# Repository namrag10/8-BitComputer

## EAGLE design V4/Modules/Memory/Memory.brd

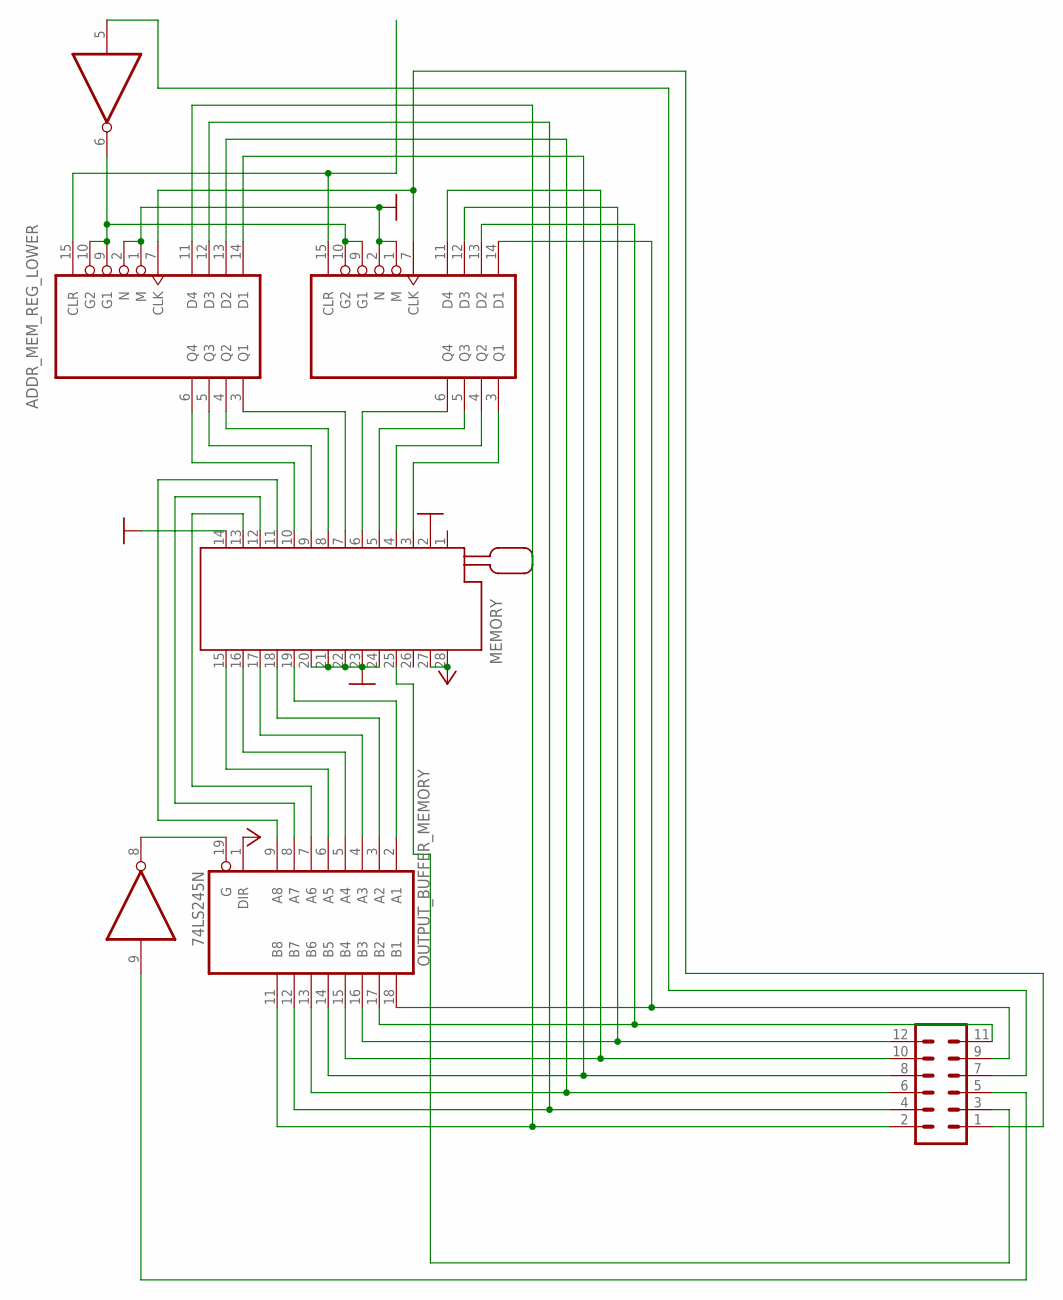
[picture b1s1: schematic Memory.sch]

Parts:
ADDR_MEM_REG_LOWER: 74LS173N; DIL16
ADDR_MEM_REG_UPPER: 74LS173N; DIL16
MEMORY: 228-1277-00-0602J
NOT_GATE1_: 74LS04N; DIL14
OUTPUT_BUFFER_MEMORY: 74LS245N; DIL20
SV1: MA06-2

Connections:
1_PLACE1: ADDR_MEM_REG_LOWER.11 (D4), OUTPUT_BUFFER_MEMORY.11 (B8), SV1.2
2_PLACE: ADDR_MEM_REG_LOWER.12 (D3), OUTPUT_BUFFER_MEMORY.12 (B7), SV1.4
4_PLACE: ADDR_MEM_REG_LOWER.13 (D2), OUTPUT_BUFFER_MEMORY.13 (B6), SV1.6
8_PLACE: ADDR_MEM_REG_LOWER.14 (D1), OUTPUT_BUFFER_MEMORY.14 (B5), SV1.8
16_PLACE: ADDR_MEM_REG_UPPER.11 (D4), OUTPUT_BUFFER_MEMORY.15 (B4), SV1.10
32_PLACE: ADDR_MEM_REG_UPPER.12 (D3), OUTPUT_BUFFER_MEMORY.16 (B3), SV1.12
64_PLACE: ADDR_MEM_REG_UPPER.13 (D2), OUTPUT_BUFFER_MEMORY.17 (B2), SV1.11
128_PLACE: ADDR_MEM_REG_UPPER.14 (D1), OUTPUT_BUFFER_MEMORY.18 (B1), SV1.9
CLOCK: ADDR_MEM_REG_LOWER.7 (CLK), ADDR_MEM_REG_UPPER.7 (CLK), SV1.1
CLR_REG: ADDR_MEM_REG_LOWER.15 (CLR), ADDR_MEM_REG_UPPER.15 (CLR)
GND: ADDR_MEM_REG_LOWER.1 (M), ADDR_MEM_REG_LOWER.2 (N), ADDR_MEM_REG_LOWER.8 (GND), ADDR_MEM_REG_UPPER.1 (M), ADDR_MEM_REG_UPPER.2 (N), ADDR_MEM_REG_UPPER.8 (GND), MEMORY.2, MEMORY.14, MEMORY.20, MEMORY.21, MEMORY.22, MEMORY.23, MEMORY.24, NOT_GATE1_.7 (GND), OUTPUT_BUFFER_MEMORY.10 (GND)
MEMORY_IN: NOT_GATE1_.5 (I), SV1.7
MEMORY_OUT: NOT_GATE1_.9 (I), SV1.5
unnamed: ADDR_MEM_REG_LOWER.6 (Q4), MEMORY.10
unnamed: ADDR_MEM_REG_LOWER.5 (Q3), MEMORY.9
unnamed: ADDR_MEM_REG_LOWER.4 (Q2), MEMORY.8
unnamed: ADDR_MEM_REG_LOWER.3 (Q1), MEMORY.7
unnamed: ADDR_MEM_REG_UPPER.6 (Q4), MEMORY.6
unnamed: ADDR_MEM_REG_UPPER.5 (Q3), MEMORY.5
unnamed: ADDR_MEM_REG_UPPER.4 (Q2), MEMORY.4
unnamed: ADDR_MEM_REG_UPPER.3 (Q1), MEMORY.3
unnamed: MEMORY.13, OUTPUT_BUFFER_MEMORY.7 (A6)
unnamed: MEMORY.12, OUTPUT_BUFFER_MEMORY.8 (A7)
unnamed: MEMORY.11, OUTPUT_BUFFER_MEMORY.9 (A8)
unnamed: MEMORY.15, OUTPUT_BUFFER_MEMORY.6 (A5)
unnamed: MEMORY.16, OUTPUT_BUFFER_MEMORY.5 (A4)
unnamed: MEMORY.17, OUTPUT_BUFFER_MEMORY.4 (A3)
unnamed: MEMORY.18, OUTPUT_BUFFER_MEMORY.3 (A2)
unnamed: MEMORY.19, OUTPUT_BUFFER_MEMORY.2 (A1)
VCC: ADDR_MEM_REG_LOWER.16 (VCC), ADDR_MEM_REG_UPPER.16 (VCC), MEMORY.27, MEMORY.28, NOT_GATE1_.14 (VCC), OUTPUT_BUFFER_MEMORY.1 (DIR), OUTPUT_BUFFER_MEMORY.20 (VCC)
~DATA/PARAM: MEMORY.25, SV1.3
~MEMORY_IN: ADDR_MEM_REG_LOWER.9 (G1), ADDR_MEM_REG_LOWER.10 (G2), ADDR_MEM_REG_UPPER.9 (G1), ADDR_MEM_REG_UPPER.10 (G2), NOT_GATE1_.6 (O)
~MEMORY_OUT: NOT_GATE1_.8 (O), OUTPUT_BUFFER_MEMORY.19 (G)

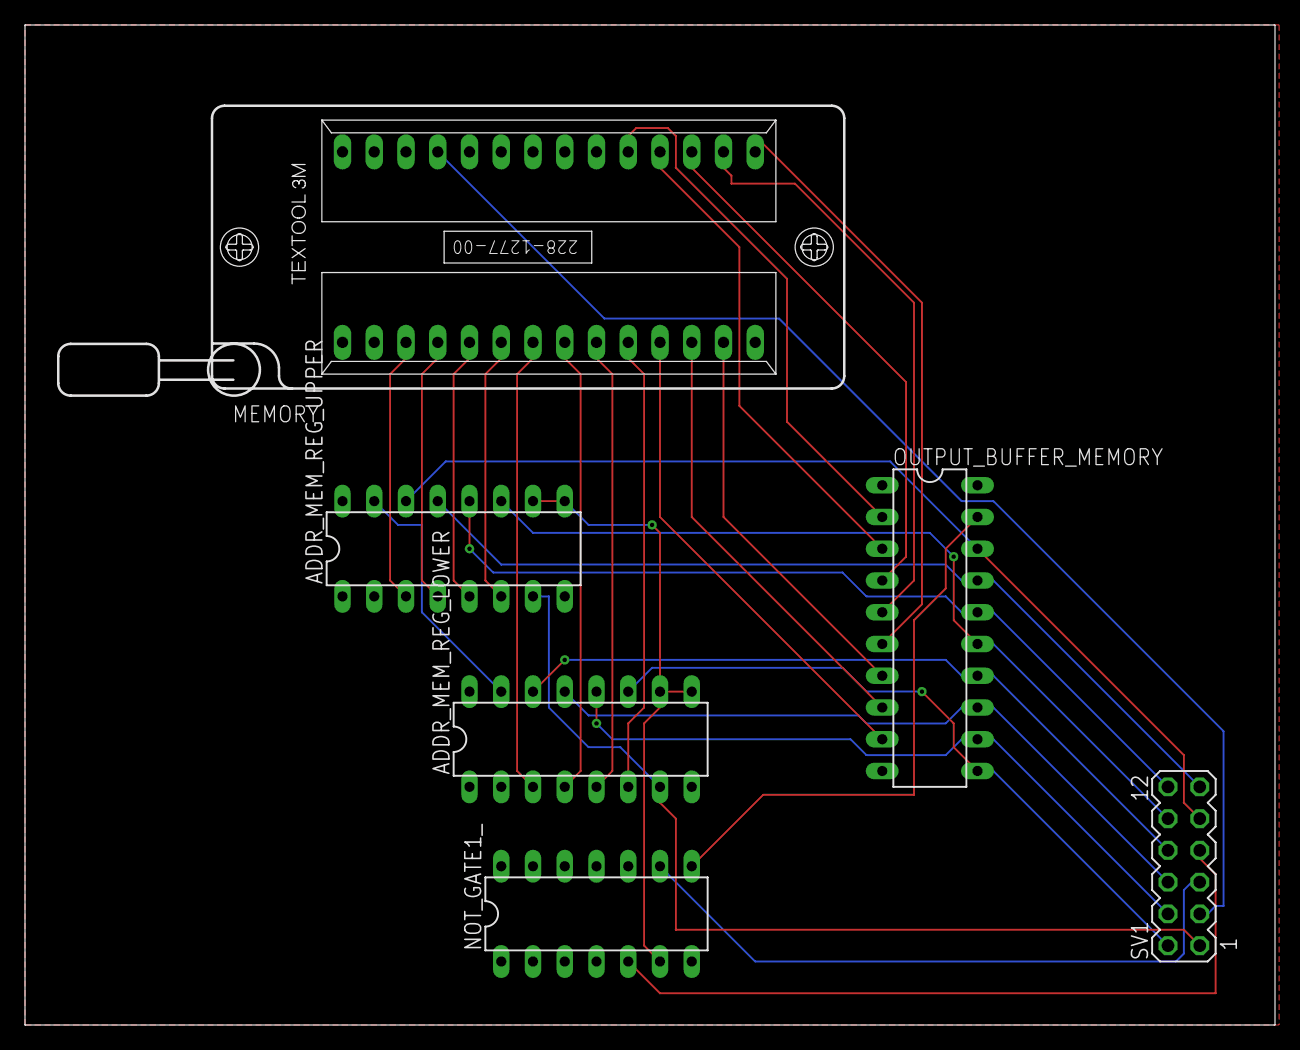
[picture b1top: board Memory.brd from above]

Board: 2 copper layers, 100.0 x 80.0 mm, 6 parts (0 on the bottom side), 33 nets.

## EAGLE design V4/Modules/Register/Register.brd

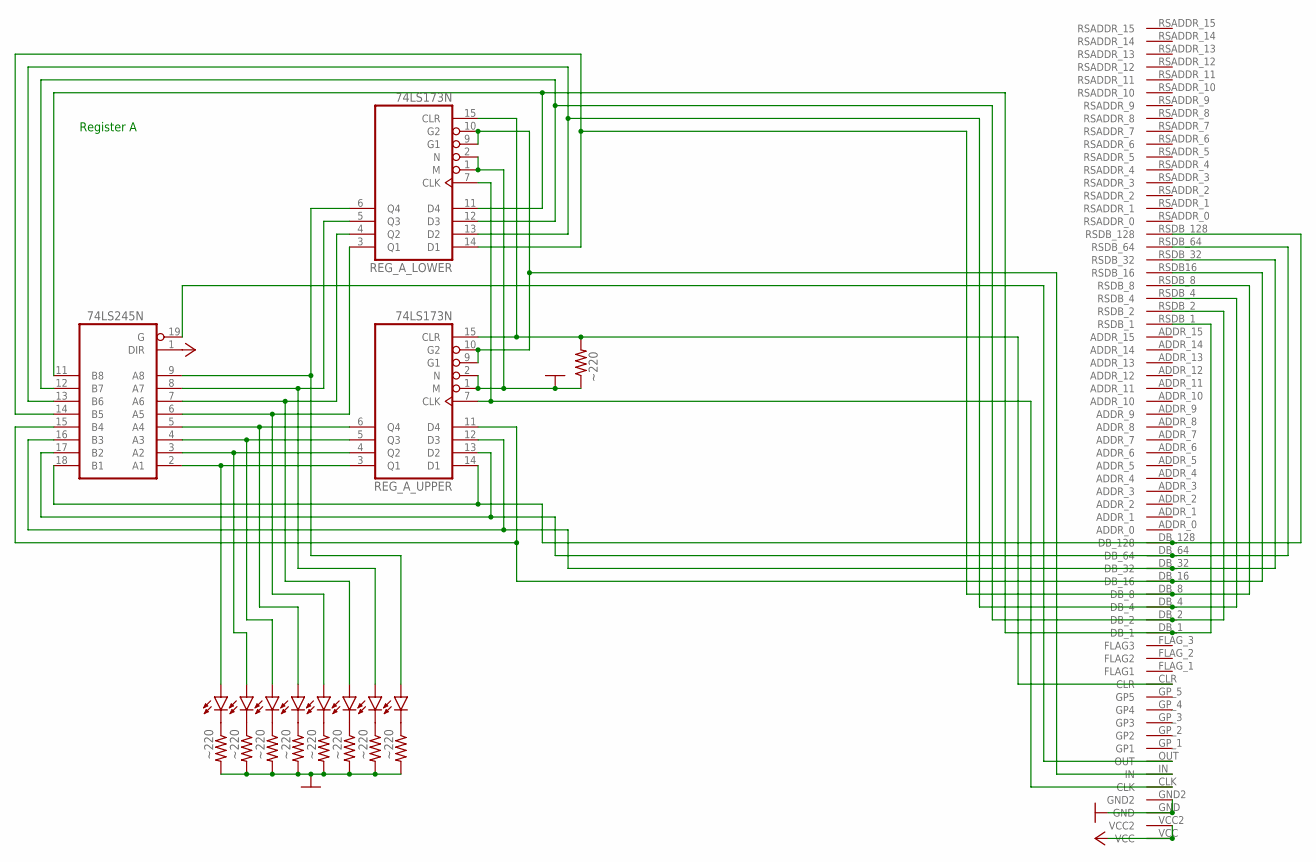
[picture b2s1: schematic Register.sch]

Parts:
LED_A_REG_1, LED_A_REG_2, LED_A_REG_3, LED_A_REG_4, LED_A_REG_5, LED_A_REG_6, LED_A_REG_7, LED_A_REG_8: LED; LED5MM
OUTPUT_BUFFER_REG_A: 74LS245N; DIL20
R1, R2, R3, R4, R5, R6, R7, R8, R9: ~220; 0204/7
REG_A_LOWER: 74LS173N; DIL16
REG_A_UPPER: 74LS173N; DIL16
U$1: BACKPLATE_INTERFACE; EDGE_FOOTPRINT

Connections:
1_PLACE1: OUTPUT_BUFFER_REG_A.11 (B8), REG_A_LOWER.11 (D4), U$1.DB_1, U$1.RSDB_1
2_PLACE: OUTPUT_BUFFER_REG_A.12 (B7), REG_A_LOWER.12 (D3), U$1.DB_2, U$1.RSDB_2
4_PLACE: OUTPUT_BUFFER_REG_A.13 (B6), REG_A_LOWER.13 (D2), U$1.DB_4, U$1.RSDB_4
8_PLACE: OUTPUT_BUFFER_REG_A.14 (B5), REG_A_LOWER.14 (D1), U$1.DB_8, U$1.RSDB_8
16_PLACE: OUTPUT_BUFFER_REG_A.15 (B4), REG_A_UPPER.11 (D4), U$1.DB_16, U$1.RSDB16 (RSDB_16)
32_PLACE: OUTPUT_BUFFER_REG_A.16 (B3), REG_A_UPPER.12 (D3), U$1.DB_32, U$1.RSDB_32
64_PLACE: OUTPUT_BUFFER_REG_A.17 (B2), REG_A_UPPER.13 (D2), U$1.DB_64, U$1.RSDB_64
128_PLACE: OUTPUT_BUFFER_REG_A.18 (B1), REG_A_UPPER.14 (D1), U$1.DB_128, U$1.RSDB_128
CLOCK: REG_A_LOWER.7 (CLK), REG_A_UPPER.7 (CLK), U$1.CLK
CLR_REG: R9.2, REG_A_LOWER.15 (CLR), REG_A_UPPER.15 (CLR), U$1.CLR
GND: OUTPUT_BUFFER_REG_A.10 (GND), R1.2, R2.2, R3.2, R4.2, R5.2, R6.2, R7.2, R8.2, R9.1, REG_A_LOWER.1 (M), REG_A_LOWER.2 (N), REG_A_LOWER.8 (GND), REG_A_UPPER.1 (M), REG_A_UPPER.2 (N), REG_A_UPPER.8 (GND), U$1.GND, U$1.GND2
unnamed: LED_A_REG_1.K (C), R1.1
unnamed: LED_A_REG_2.K (C), R2.1
unnamed: LED_A_REG_3.K (C), R3.1
unnamed: LED_A_REG_4.K (C), R4.1
unnamed: LED_A_REG_5.K (C), R5.1
unnamed: LED_A_REG_6.K (C), R6.1
unnamed: LED_A_REG_7.K (C), R7.1
unnamed: LED_A_REG_8.K (C), R8.1
REG_A_1PLACE: LED_A_REG_1.A, OUTPUT_BUFFER_REG_A.9 (A8), REG_A_LOWER.6 (Q4)
REG_A_2PLACE: LED_A_REG_2.A, OUTPUT_BUFFER_REG_A.8 (A7), REG_A_LOWER.5 (Q3)
REG_A_4PLACE: LED_A_REG_3.A, OUTPUT_BUFFER_REG_A.7 (A6), REG_A_LOWER.4 (Q2)
REG_A_8PLACE: LED_A_REG_4.A, OUTPUT_BUFFER_REG_A.6 (A5), REG_A_LOWER.3 (Q1)
REG_A_16PLACE: LED_A_REG_5.A, OUTPUT_BUFFER_REG_A.5 (A4), REG_A_UPPER.6 (Q4)
REG_A_32PLACE: LED_A_REG_6.A, OUTPUT_BUFFER_REG_A.4 (A3), REG_A_UPPER.5 (Q3)
REG_A_64PLACE: LED_A_REG_7.A, OUTPUT_BUFFER_REG_A.3 (A2), REG_A_UPPER.4 (Q2)
REG_A_128PLACE: LED_A_REG_8.A, OUTPUT_BUFFER_REG_A.2 (A1), REG_A_UPPER.3 (Q1)
REG_A_IN: REG_A_LOWER.9 (G1), REG_A_LOWER.10 (G2), REG_A_UPPER.9 (G1), REG_A_UPPER.10 (G2), U$1.IN
REG_A_OUT: OUTPUT_BUFFER_REG_A.19 (G), U$1.OUT
VCC: OUTPUT_BUFFER_REG_A.1 (DIR), OUTPUT_BUFFER_REG_A.20 (VCC), REG_A_LOWER.16 (VCC), REG_A_UPPER.16 (VCC), U$1.VCC, U$1.VCC2

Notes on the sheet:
Register A

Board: 2 copper layers, 21 parts (0 on the bottom side), 30 nets, no tracks yet.

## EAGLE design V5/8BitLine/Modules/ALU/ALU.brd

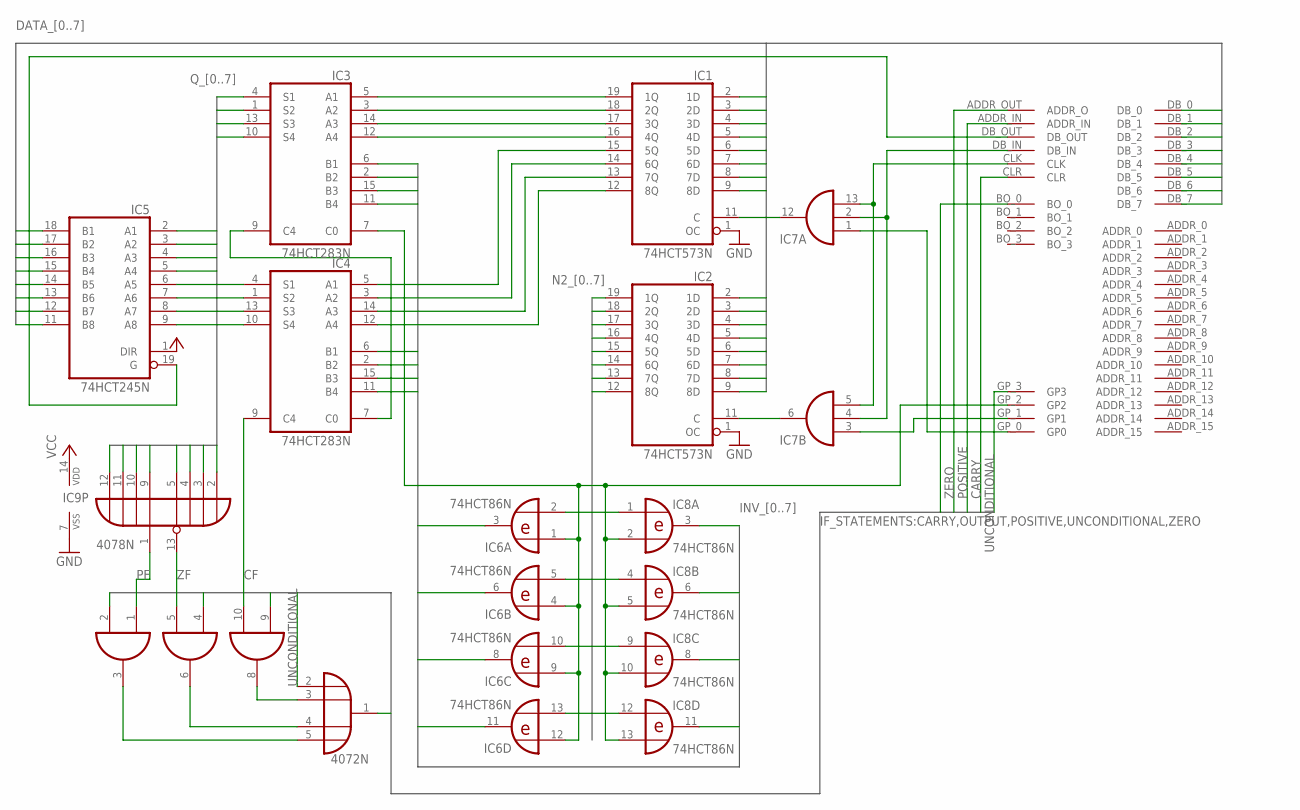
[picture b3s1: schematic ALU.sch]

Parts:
IC1, IC2: 74HCT573N; DIL20
IC3, IC4: 74HCT283N; DIL16
IC5: 74HCT245N; DIL20
IC6, IC8: 74HCT86N; DIL14
IC7: 74HCT11N; DIL14
IC9: 4078N; DIL14
IC10: 74HCT08N; DIL14
IC11: 4072N; DIL14
U$1: BACKPLATE_INTERFACEEDGE_FINGER; BACK_INTERFACE-FOOT

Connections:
CARRY: IC10.9 (I0), U$1.CLR
CF: IC4.9 (C4), IC10.10 (I1)
DATA_0: IC1.2 (1D), IC2.2 (1D), IC5.18 (B1), U$1.DB_0
DATA_1: IC1.3 (2D), IC2.3 (2D), IC5.17 (B2), U$1.DB_1
DATA_2: IC1.4 (3D), IC2.4 (3D), IC5.16 (B3), U$1.DB_2
DATA_3: IC1.5 (4D), IC2.5 (4D), IC5.15 (B4), U$1.DB_3
DATA_4: IC1.6 (5D), IC2.6 (5D), IC5.14 (B5), U$1.DB_4
DATA_5: IC1.7 (6D), IC2.7 (6D), IC5.13 (B6), U$1.DB_5
DATA_6: IC1.8 (7D), IC2.8 (7D), IC5.12 (B7), U$1.DB_6
DATA_7: IC1.9 (8D), IC2.9 (8D), IC5.11 (B8), U$1.DB_7
GND: IC1.1 (OC), IC1.10 (GND), IC2.1 (OC), IC2.10 (GND), IC3.8 (GND), IC4.8 (GND), IC5.10 (GND), IC6.7 (GND), IC7.7 (GND), IC8.7 (GND), IC9.7 (VSS), IC10.7 (GND), U$1.GND_0 (GND), U$1.GND_1 (GND)
INV_0: IC3.6 (B1), IC6.3 (O)
INV_1: IC3.2 (B2), IC6.6 (O)
INV_2: IC3.15 (B3), IC6.8 (O)
INV_3: IC3.11 (B4), IC6.11 (O)
INV_4: IC4.6 (B1), IC8.3 (O)
INV_5: IC4.2 (B2), IC8.6 (O)
INV_6: IC4.15 (B3), IC8.8 (O)
INV_7: IC4.11 (B4), IC8.11 (O)
LOWER_BYTE_SIGNAL: IC7.1 (I0), U$1.GP_0 (GP0)
N2_0: IC2.19 (1Q), IC6.2 (I1)
N2_1: IC2.18 (2Q), IC6.5 (I1)
N2_2: IC2.17 (3Q), IC6.10 (I1)
N2_3: IC2.16 (4Q), IC6.13 (I1)
N2_4: IC2.15 (5Q), IC8.1 (I0)
N2_5: IC2.14 (6Q), IC8.4 (I0)
N2_6: IC2.13 (7Q), IC8.9 (I0)
N2_7: IC2.12 (8Q), IC8.12 (I0)
unnamed: IC1.19 (1Q), IC3.5 (A1)
unnamed: IC1.18 (2Q), IC3.3 (A2)
unnamed: IC1.17 (3Q), IC3.14 (A3)
unnamed: IC1.16 (4Q), IC3.12 (A4)
unnamed: IC1.15 (5Q), IC4.5 (A1)
unnamed: IC1.14 (6Q), IC4.3 (A2)
unnamed: IC1.13 (7Q), IC4.14 (A3)
unnamed: IC1.12 (8Q), IC4.12 (A4)
unnamed: IC7.5 (I2), IC7.13 (I2), U$1.CLK
unnamed: IC7.2 (I1), IC7.4 (I1), U$1.DB_IN
unnamed: IC10.8 (O), IC11.3 (I1)
unnamed: IC10.6 (O), IC11.4 (I2)
unnamed: IC1.11 (C), IC7.12 (O)
unnamed: IC2.11 (C), IC7.6 (O)
unnamed: IC5.19 (G), U$1.DB_OUT
unnamed: IC10.3 (O), IC11.5 (I3)
unnamed: IC3.9 (C4), IC4.7 (C0)
OUTPUT: IC11.1 (O), U$1.BO_0
PF: IC9.1, IC10.1 (I0)
POSITIVE: IC10.2 (I1), U$1.ADDR_IN
Q_0: IC3.4 (S1), IC5.2 (A1), IC9.2 (I0)
Q_1: IC3.1 (S2), IC5.3 (A2), IC9.3 (I1)
Q_2: IC3.13 (S3), IC5.4 (A3), IC9.4 (I2)
Q_3: IC3.10 (S4), IC5.5 (A4), IC9.5 (I3)
Q_4: IC4.4 (S1), IC5.6 (A5), IC9.9 (I4)
Q_5: IC4.1 (S2), IC5.7 (A6), IC9.10 (I5)
Q_6: IC4.13 (S3), IC5.8 (A7), IC9.11 (I6)
Q_7: IC4.10 (S4), IC5.9 (A8), IC9.12 (I7)
SUBTRACT_MODE: IC3.7 (C0), IC6.1 (I0), IC6.4 (I0), IC6.9 (I0), IC6.12 (I0), IC8.2 (I1), IC8.5 (I1), IC8.10 (I1), IC8.13 (I1), U$1.GP_2 (GP2)
UNCONDITIONAL: IC11.2 (I0), U$1.GP_3 (GP3)
UPPER_BYTE_SIGNAL: IC7.3 (I0), U$1.GP_1 (GP1)
VCC: IC1.20 (VCC), IC2.20 (VCC), IC3.16 (VCC), IC4.16 (VCC), IC5.1 (DIR), IC5.20 (VCC), IC6.14 (VCC), IC7.14 (VCC), IC8.14 (VCC), IC9.14 (VDD), IC10.14 (VCC), U$1.VCC_0 (VCC), U$1.VCC_1 (VCC)
VDD: IC11.14 (VDD)
VSS: IC11.7 (VSS)
ZERO: IC10.4 (I0), U$1.ADDR_OUT (ADDR_O)
ZF: IC9.13 (J), IC10.5 (I1)

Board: 2 copper layers, 12 parts (0 on the bottom side), 62 nets, no tracks yet.

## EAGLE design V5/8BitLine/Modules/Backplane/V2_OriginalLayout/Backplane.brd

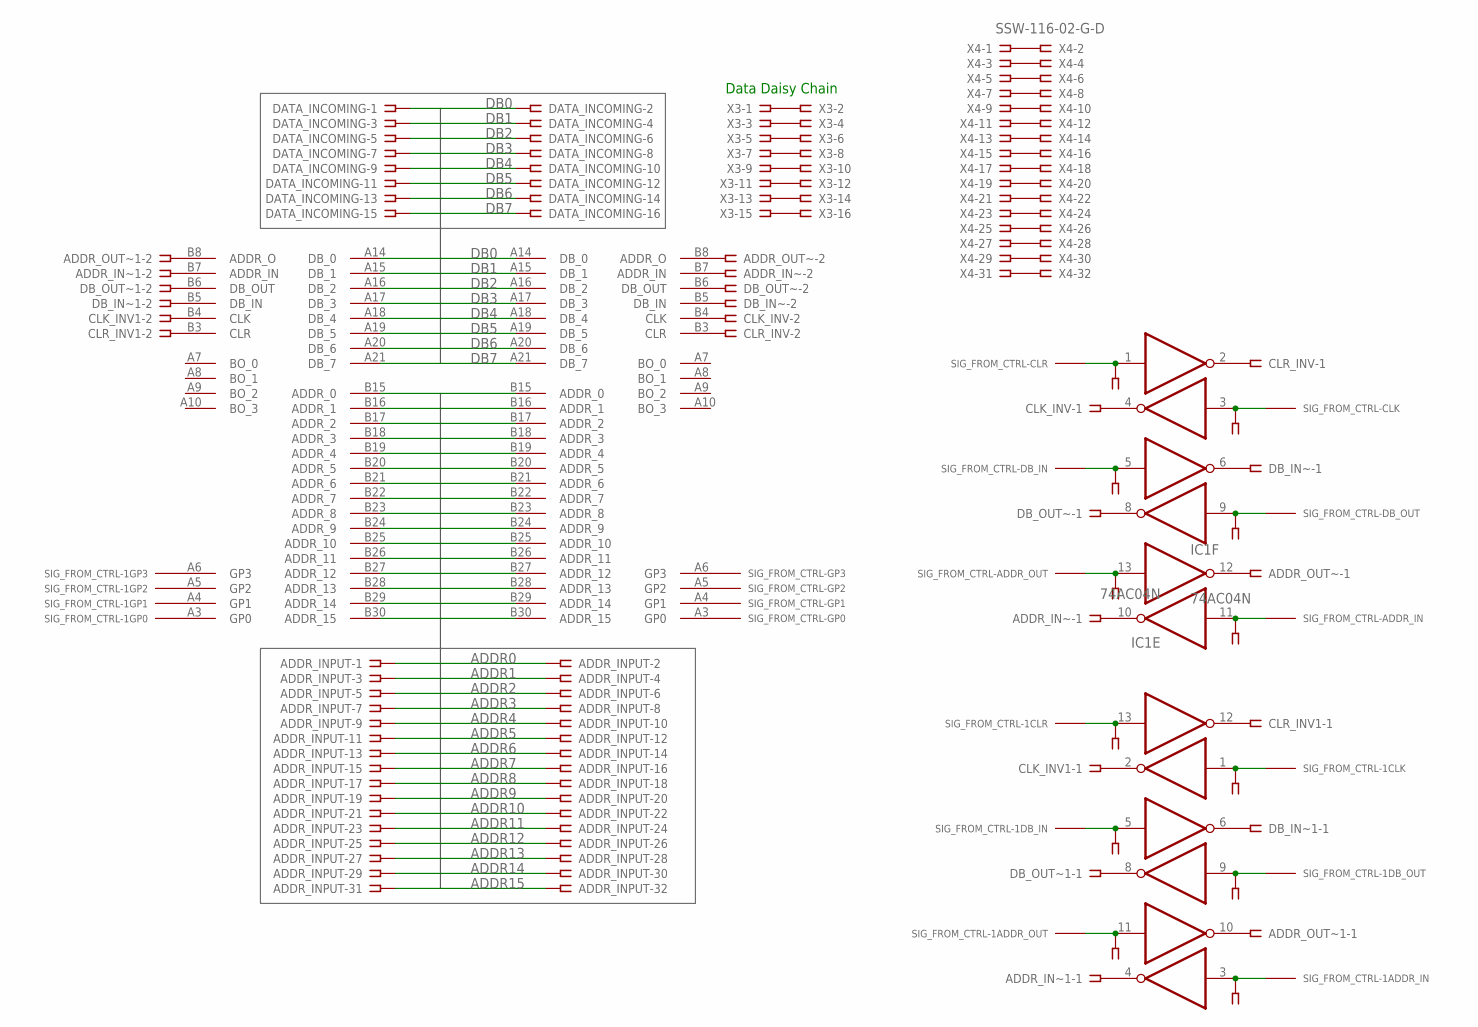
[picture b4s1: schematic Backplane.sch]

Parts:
ADDR_INPUT: SSW-116-02-G-D
ADDR_IN~, ADDR_IN~1: SSW-103-02-G-S
ADDR_OUT~, ADDR_OUT~1: SSW-103-02-G-S
CLK_INV, CLK_INV1: SSW-103-02-G-S
CLR_INV, CLR_INV1: SSW-103-02-G-S
DATA_INCOMING: SSW-108-02-G-D
DB_IN~, DB_IN~1: SSW-103-02-G-S
DB_OUT~, DB_OUT~1: SSW-103-02-G-S
IC1, IC2: 74AC04N; DIL14
SIG_FROM_CTRL-, SIG_FROM_CTRL-1: CONTROL_SIG-INT; CONTROL_SIG-INT-FOOT
U$1, U$2: BACKPLATE_INTERFACEHEADER; PCI_INTERFACE
X3: SSW-108-02-G-D
X4: SSW-116-02-G-D

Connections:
ADDR0: ADDR_INPUT.1, ADDR_INPUT.2, U$1.B15 (ADDR_0), U$2.B15 (ADDR_0)
ADDR1: ADDR_INPUT.3, ADDR_INPUT.4, U$1.B16 (ADDR_1), U$2.B16 (ADDR_1)
ADDR2: ADDR_INPUT.5, ADDR_INPUT.6, U$1.B17 (ADDR_2), U$2.B17 (ADDR_2)
ADDR3: ADDR_INPUT.7, ADDR_INPUT.8, U$1.B18 (ADDR_3), U$2.B18 (ADDR_3)
ADDR4: ADDR_INPUT.9, ADDR_INPUT.10, U$1.B19 (ADDR_4), U$2.B19 (ADDR_4)
ADDR5: ADDR_INPUT.11, ADDR_INPUT.12, U$1.B20 (ADDR_5), U$2.B20 (ADDR_5)
ADDR6: ADDR_INPUT.13, ADDR_INPUT.14, U$1.B21 (ADDR_6), U$2.B21 (ADDR_6)
ADDR7: ADDR_INPUT.15, ADDR_INPUT.16, U$1.B22 (ADDR_7), U$2.B22 (ADDR_7)
ADDR8: ADDR_INPUT.17, ADDR_INPUT.18, U$1.B23 (ADDR_8), U$2.B23 (ADDR_8)
ADDR9: ADDR_INPUT.19, ADDR_INPUT.20, U$1.B24 (ADDR_9), U$2.B24 (ADDR_9)
ADDR10: ADDR_INPUT.21, ADDR_INPUT.22, U$1.B25 (ADDR_10), U$2.B25 (ADDR_10)
ADDR11: ADDR_INPUT.23, ADDR_INPUT.24, U$1.B26 (ADDR_11), U$2.B26 (ADDR_11)
ADDR12: ADDR_INPUT.25, ADDR_INPUT.26, U$1.B27 (ADDR_12), U$2.B27 (ADDR_12)
ADDR13: ADDR_INPUT.27, ADDR_INPUT.28, U$1.B28 (ADDR_13), U$2.B28 (ADDR_13)
ADDR14: ADDR_INPUT.29, ADDR_INPUT.30, U$1.B29 (ADDR_14), U$2.B29 (ADDR_14)
ADDR15: ADDR_INPUT.31, ADDR_INPUT.32, U$1.B30 (ADDR_15), U$2.B30 (ADDR_15)
DB0: DATA_INCOMING.1, DATA_INCOMING.2, U$1.A14 (DB_0), U$2.A14 (DB_0)
DB1: DATA_INCOMING.3, DATA_INCOMING.4, U$1.A15 (DB_1), U$2.A15 (DB_1)
DB2: DATA_INCOMING.5, DATA_INCOMING.6, U$1.A16 (DB_2), U$2.A16 (DB_2)
DB3: DATA_INCOMING.7, DATA_INCOMING.8, U$1.A17 (DB_3), U$2.A17 (DB_3)
DB4: DATA_INCOMING.9, DATA_INCOMING.10, U$1.A18 (DB_4), U$2.A18 (DB_4)
DB5: DATA_INCOMING.11, DATA_INCOMING.12, U$1.A19 (DB_5), U$2.A19 (DB_5)
DB6: DATA_INCOMING.13, DATA_INCOMING.14, U$1.A20 (DB_6), U$2.A20 (DB_6)
DB7: DATA_INCOMING.15, DATA_INCOMING.16, U$1.A21 (DB_7), U$2.A21 (DB_7)
GND: IC1.7 (GND), IC2.7 (GND), SIG_FROM_CTRL-.GND, SIG_FROM_CTRL-1.GND, U$1.B2 (GND), U$1.B31 (GND), U$2.B2 (GND), U$2.B31 (GND)
unnamed: CLR_INV.2, U$2.B3 (CLR)
unnamed: CLR_INV.3, IC1.1 (I), SIG_FROM_CTRL-.CLR (0)
unnamed: CLK_INV.2, U$2.B4 (CLK)
unnamed: DB_IN~.2, U$2.B5 (DB_IN)
unnamed: DB_OUT~.2, U$2.B6 (DB_OUT)
unnamed: SIG_FROM_CTRL-.GP0 (0), U$2.A3 (GP0)
unnamed: SIG_FROM_CTRL-.GP1 (0), U$2.A4 (GP1)
unnamed: CLK_INV.3, IC1.3 (I), SIG_FROM_CTRL-.CLK (0)
unnamed: DB_IN~.3, IC1.5 (I), SIG_FROM_CTRL-.DB_IN (0)
unnamed: DB_OUT~.3, IC1.9 (I), SIG_FROM_CTRL-.DB_OUT (0)
unnamed: SIG_FROM_CTRL-.GP2 (0), U$2.A5 (GP2)
unnamed: SIG_FROM_CTRL-.GP3 (0), U$2.A6 (GP3)
unnamed: ADDR_OUT~.3, IC1.13 (I), SIG_FROM_CTRL-.ADDR_OT (0)
unnamed: ADDR_IN~.1, IC1.10 (O)
unnamed: CLR_INV.1, IC1.2 (O)
unnamed: CLK_INV.1, IC1.4 (O)
unnamed: DB_IN~.1, IC1.6 (O)
unnamed: DB_OUT~.1, IC1.8 (O)
unnamed: ADDR_IN~.3, IC1.11 (I), SIG_FROM_CTRL-.ADDR_IN (0)
unnamed: ADDR_OUT~.1, IC1.12 (O)
unnamed: ADDR_OUT~.2, U$2.B8 (ADDR_O)
unnamed: ADDR_IN~.2, U$2.B7 (ADDR_IN)
unnamed: X3.1, X3.2
unnamed: X3.3, X3.4
unnamed: X3.5, X3.6
unnamed: X3.7, X3.8
unnamed: X3.9, X3.10
unnamed: X3.11, X3.12
unnamed: X3.13, X3.14
unnamed: X3.15, X3.16
unnamed: X4.1, X4.2
unnamed: X4.3, X4.4
unnamed: X4.5, X4.6
unnamed: X4.7, X4.8
unnamed: X4.9, X4.10
unnamed: X4.11, X4.12
unnamed: X4.13, X4.14
unnamed: X4.15, X4.16
unnamed: X4.17, X4.18
unnamed: X4.19, X4.20
unnamed: X4.21, X4.22
unnamed: X4.23, X4.24
unnamed: X4.25, X4.26
unnamed: X4.27, X4.28
unnamed: X4.29, X4.30
unnamed: X4.31, X4.32
unnamed: CLR_INV1.3, IC2.13 (I), SIG_FROM_CTRL-1.CLR (0)
unnamed: CLK_INV1.3, IC2.1 (I), SIG_FROM_CTRL-1.CLK (0)
unnamed: DB_IN~1.3, IC2.5 (I), SIG_FROM_CTRL-1.DB_IN (0)
unnamed: DB_OUT~1.3, IC2.9 (I), SIG_FROM_CTRL-1.DB_OUT (0)
unnamed: CLK_INV1.1, IC2.2 (O)
unnamed: ADDR_IN~1.1, IC2.4 (O)
unnamed: DB_IN~1.1, IC2.6 (O)
unnamed: DB_OUT~1.1, IC2.8 (O)
unnamed: ADDR_OUT~1.3, IC2.11 (I), SIG_FROM_CTRL-1.ADDR_OT (0)
unnamed: ADDR_IN~1.3, IC2.3 (I), SIG_FROM_CTRL-1.ADDR_IN (0)
unnamed: ADDR_OUT~1.1, IC2.10 (O)
unnamed: CLR_INV1.1, IC2.12 (O)
unnamed: CLK_INV1.2, U$1.B4 (CLK)
unnamed: CLR_INV1.2, U$1.B3 (CLR)
unnamed: DB_IN~1.2, U$1.B5 (DB_IN)
unnamed: DB_OUT~1.2, U$1.B6 (DB_OUT)
unnamed: ADDR_OUT~1.2, U$1.B8 (ADDR_O)
unnamed: ADDR_IN~1.2, U$1.B7 (ADDR_IN)
unnamed: SIG_FROM_CTRL-1.GP0 (0), U$1.A3 (GP0)
unnamed: SIG_FROM_CTRL-1.GP1 (0), U$1.A4 (GP1)
unnamed: SIG_FROM_CTRL-1.GP2 (0), U$1.A5 (GP2)
unnamed: SIG_FROM_CTRL-1.GP3 (0), U$1.A6 (GP3)
VCC: IC1.14 (VCC), IC2.14 (VCC), SIG_FROM_CTRL-.VCC, SIG_FROM_CTRL-1.VCC, U$1.A2 (VCC), U$1.A31 (VCC), U$2.A2 (VCC), U$2.A31 (VCC)

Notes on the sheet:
Data Daisy Chain

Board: 2 copper layers, 22 parts (0 on the bottom side), 94 nets, no tracks yet.

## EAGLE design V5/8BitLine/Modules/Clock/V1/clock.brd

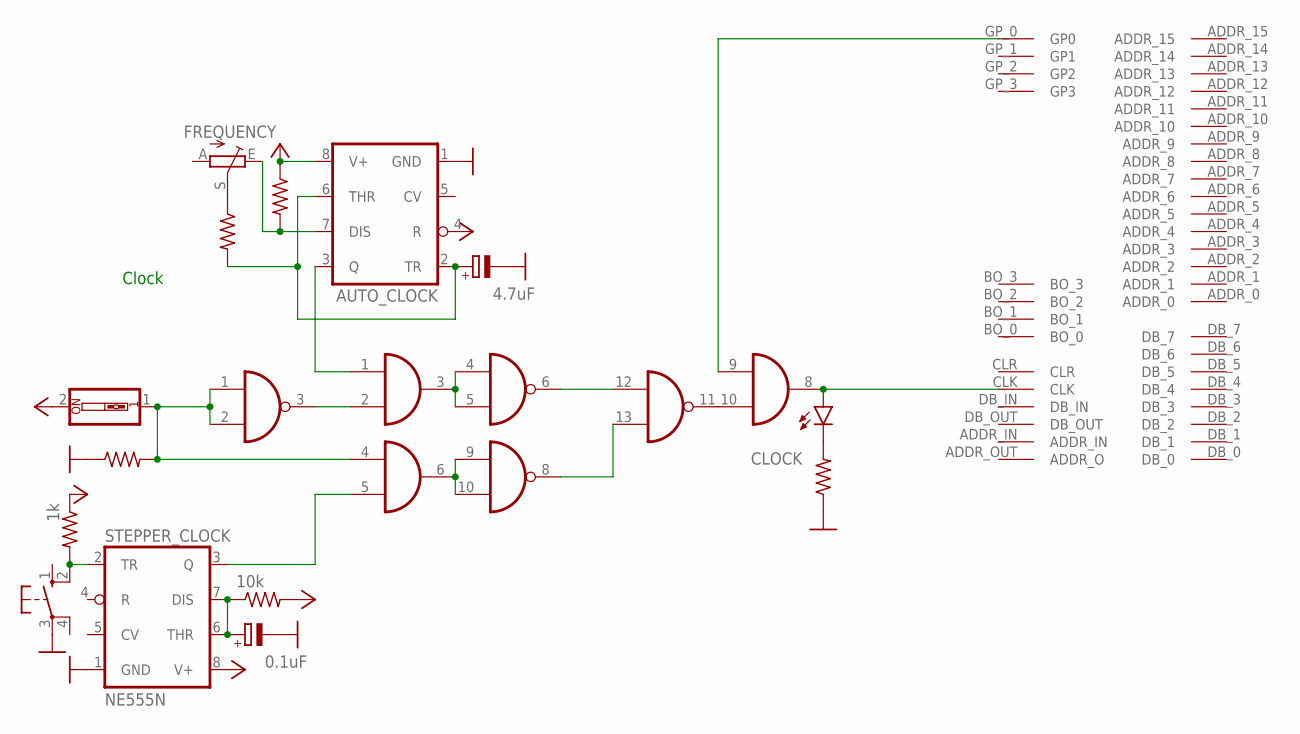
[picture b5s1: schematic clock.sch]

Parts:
AND_GATE_: 74LS08N; DIL14
AUTO_CLOCK: NE555N; DIL08
C1: 4.7uF; E2-5
C2: 0.1uF; E2-5
CLK_MODE: SWITCH; EDG-01
CLK_TRIGGER: SWITCH; B3F-10XX
CLOCK: Yellow; LED5MM
FREQUENCY: 100k; RJ9W
NAND: 74ACT00N; DIL14
R1, R2: 1k; 0204/7
R3: 10k; 0204/7
R4, R6: 220; 0204/7
R5: ~220; 0204/7
STEPPER_CLOCK: NE555N; DIL08
U$1: BACKPLATE_INTERFACEEDGE_FINGER; BACK_INTERFACE-FOOT

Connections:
CLOCK: AND_GATE_.8 (O), CLOCK.A, U$1.CLK
GND: AND_GATE_.7 (GND), AUTO_CLOCK.1 (GND), C1.-, C2.-, CLK_TRIGGER.3, NAND.7 (GND), R4.1, R5.1, STEPPER_CLOCK.1 (GND), U$1.GND_0 (GND), U$1.GND_1 (GND)
HLT: AND_GATE_.9 (I0), U$1.GP_0 (GP0)
MODE_SIGNAL: AND_GATE_.4 (I0), CLK_MODE.1, NAND.1 (I0), NAND.2 (I1), R4.2
unnamed: C2.+, R3.1, STEPPER_CLOCK.6 (THR), STEPPER_CLOCK.7 (DIS)
unnamed: CLK_TRIGGER.2 (S1), R2.2, STEPPER_CLOCK.2 (TR)
unnamed: CLOCK.K (C), R5.2
unnamed: AND_GATE_.5 (I1), STEPPER_CLOCK.3 (Q)
unnamed: AND_GATE_.3 (O), NAND.4 (I0), NAND.5 (I1)
unnamed: AND_GATE_.1 (I0), AUTO_CLOCK.3 (Q)
unnamed: AND_GATE_.6 (O), NAND.9 (I0), NAND.10 (I1)
unnamed: NAND.8 (O), NAND.13 (I1)
unnamed: AND_GATE_.2 (I1), NAND.3 (O)
unnamed: NAND.6 (O), NAND.12 (I0)
unnamed: AND_GATE_.10 (I1), NAND.11 (O)
unnamed: AUTO_CLOCK.2 (TR), AUTO_CLOCK.6 (THR), C1.+, R6.2
unnamed: FREQUENCY.S, R6.1
unnamed: AUTO_CLOCK.7 (DIS), FREQUENCY.E, R1.2
VCC: AND_GATE_.14 (VCC), AUTO_CLOCK.4 (R), AUTO_CLOCK.8 (V+), CLK_MODE.2, NAND.14 (VCC), R1.1, R2.1, R3.2, STEPPER_CLOCK.8 (V+), U$1.VCC_0 (VCC), U$1.VCC_1 (VCC)

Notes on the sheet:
Clock

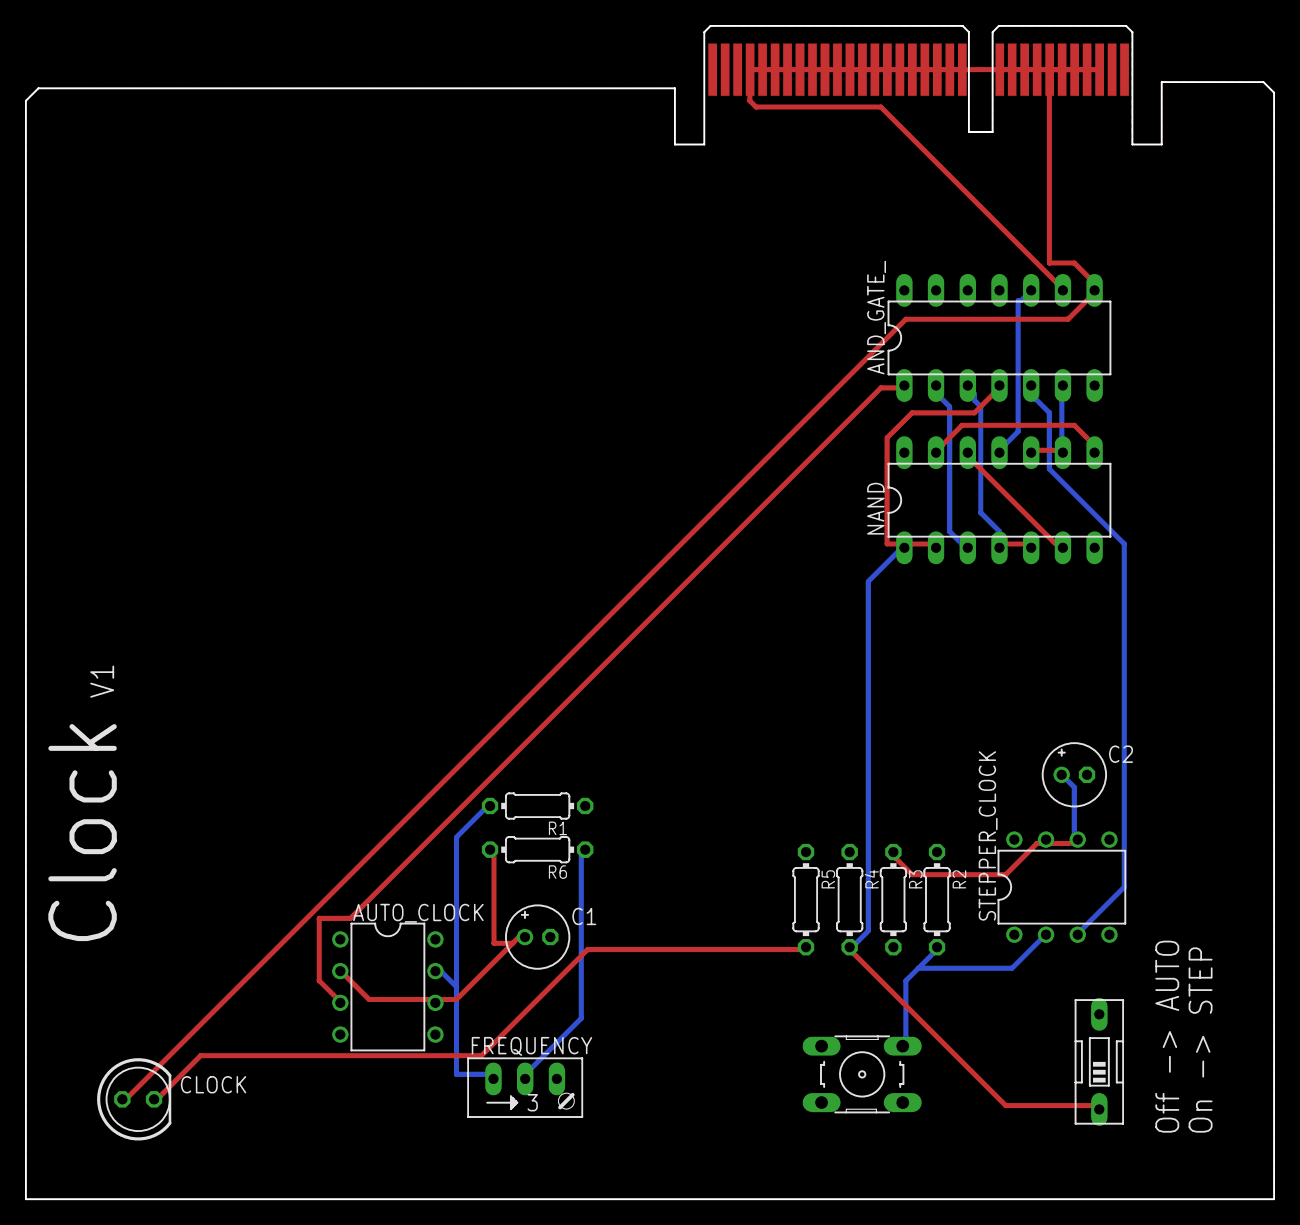
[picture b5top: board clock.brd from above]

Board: 2 copper layers, 100.0 x 94.0 mm, 17 parts (0 on the bottom side), 19 nets.

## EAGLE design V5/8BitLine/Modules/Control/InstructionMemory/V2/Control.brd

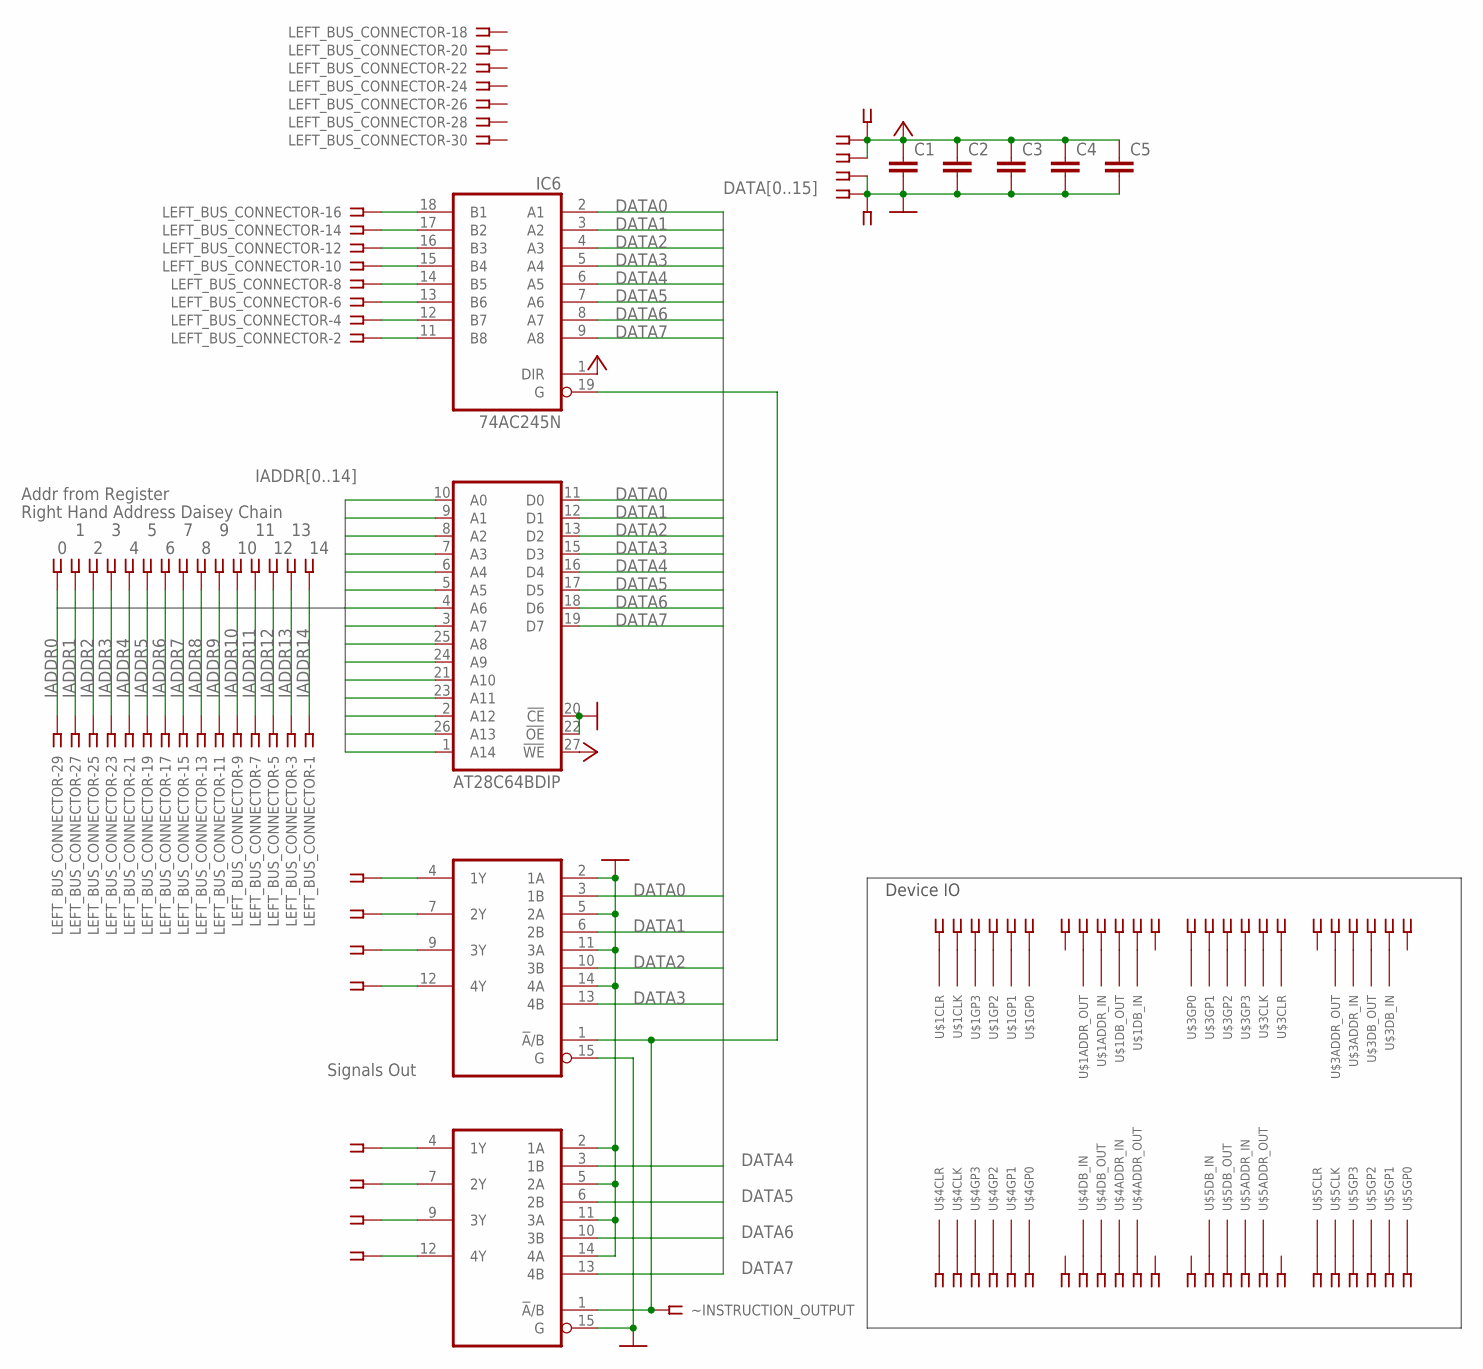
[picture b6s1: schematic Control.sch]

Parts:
C1, C2, C3, C4, C5: C2.5/2; C2.5-2
IC4, IC5: 74AC157N; DIL16
IC6: 74AC245N; DIL20
LEFT_BUS_CONNECTOR: SSW-115-02-G-D
MEZZANINE: SSW-104-02-G-S
U$1, U$3, U$4, U$5: CONTROL_SIG-INT; CONTROL_SIG-INT-FOOT
U$2: AT28C64BDIP; DIP28-WIDE
X1, X2, X3, X4, X6, X7, X8, X9: SSW-106-02-G-S
X5: SSW-108-02-G-S
X11: SSW-102-02-G-S
X12: SSW-115-02-G-S
~INSTRUCTION_OUTPUT: SSW-101-02-G-S

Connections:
DATA0: IC4.3 (1B), IC6.2 (A1), U$2.11 (D0)
DATA1: IC4.6 (2B), IC6.3 (A2), U$2.12 (D1)
DATA2: IC4.10 (3B), IC6.4 (A3), U$2.13 (D2)
DATA3: IC4.13 (4B), IC6.5 (A4), U$2.15 (D3)
DATA4: IC5.3 (1B), IC6.6 (A5), U$2.16 (D4)
DATA5: IC5.6 (2B), IC6.7 (A6), U$2.17 (D5)
DATA6: IC5.10 (3B), IC6.8 (A7), U$2.18 (D6)
DATA7: IC5.13 (4B), IC6.9 (A8), U$2.19 (D7)
GND: C1.2, C2.2, C3.2, C4.2, C5.2, IC4.2 (1A), IC4.5 (2A), IC4.8 (GND), IC4.11 (3A), IC4.14 (4A), IC4.15 (G), IC5.2 (1A), IC5.5 (2A), IC5.8 (GND), IC5.11 (3A), IC5.14 (4A), IC5.15 (G), IC6.10 (GND), MEZZANINE.3, MEZZANINE.4, U$1.GND, U$2.14 (GND), U$2.20 (!CE), U$2.22 (!OE), U$3.GND, U$4.GND, U$5.GND, X11.2
IADDR0: LEFT_BUS_CONNECTOR.29, U$2.10 (A0), X12.1
IADDR1: LEFT_BUS_CONNECTOR.27, U$2.9 (A1), X12.2
IADDR2: LEFT_BUS_CONNECTOR.25, U$2.8 (A2), X12.3
IADDR3: LEFT_BUS_CONNECTOR.23, U$2.7 (A3), X12.4
IADDR4: LEFT_BUS_CONNECTOR.21, U$2.6 (A4), X12.5
IADDR5: LEFT_BUS_CONNECTOR.19, U$2.5 (A5), X12.6
IADDR6: LEFT_BUS_CONNECTOR.17, U$2.4 (A6), X12.7
IADDR7: LEFT_BUS_CONNECTOR.15, U$2.3 (A7), X12.8
IADDR8: LEFT_BUS_CONNECTOR.13, U$2.25 (A8), X12.9
IADDR9: LEFT_BUS_CONNECTOR.11, U$2.24 (A9), X12.10
IADDR10: LEFT_BUS_CONNECTOR.9, U$2.21 (A10), X12.11
IADDR11: LEFT_BUS_CONNECTOR.7, U$2.23 (A11), X12.12
IADDR12: LEFT_BUS_CONNECTOR.5, U$2.2 (A12), X12.13
IADDR13: LEFT_BUS_CONNECTOR.3, U$2.26 (A13), X12.14
IADDR14: LEFT_BUS_CONNECTOR.1, U$2.1 (A14), X12.15
I_OUT: IC4.1 (!A!/B), IC5.1 (!A!/B), IC6.19 (G), ~INSTRUCTION_OUTPUT.1
unnamed: U$1.GP0 (0), X1.6
unnamed: U$1.GP1 (0), X1.5
unnamed: U$1.GP2 (0), X1.4
unnamed: U$1.GP3 (0), X1.3
unnamed: U$1.CLK (0), X1.2
unnamed: U$1.CLR (0), X1.1
unnamed: U$1.DB_IN (0), X2.2
unnamed: U$1.DB_OUT (0), X2.3
unnamed: U$1.ADDR_IN (0), X2.4
unnamed: U$1.ADDR_OT (0), X2.5
unnamed: U$3.GP0 (0), X3.6
unnamed: U$3.GP1 (0), X3.5
unnamed: U$3.GP2 (0), X3.4
unnamed: U$3.GP3 (0), X3.3
unnamed: U$3.CLK (0), X3.2
unnamed: U$3.CLR (0), X3.1
unnamed: U$3.DB_IN (0), X4.2
unnamed: U$3.DB_OUT (0), X4.3
unnamed: U$3.ADDR_IN (0), X4.4
unnamed: U$3.ADDR_OT (0), X4.5
unnamed: U$4.CLR (0), X9.1
unnamed: U$4.CLK (0), X9.2
unnamed: U$4.GP0 (0), X9.6
unnamed: U$4.GP1 (0), X9.5
unnamed: U$4.GP2 (0), X9.4
unnamed: U$4.GP3 (0), X9.3
unnamed: U$4.DB_IN (0), X8.2
unnamed: U$4.DB_OUT (0), X8.3
unnamed: U$4.ADDR_IN (0), X8.4
unnamed: U$4.ADDR_OT (0), X8.5
unnamed: U$5.GP0 (0), X6.6
unnamed: U$5.GP3 (0), X6.3
unnamed: U$5.GP2 (0), X6.4
unnamed: U$5.GP1 (0), X6.5
unnamed: U$5.CLK (0), X6.2
unnamed: U$5.CLR (0), X6.1
unnamed: U$5.DB_IN (0), X7.2
unnamed: U$5.DB_OUT (0), X7.3
unnamed: U$5.ADDR_IN (0), X7.4
unnamed: U$5.ADDR_OT (0), X7.5
O_DB0: IC6.18 (B1), LEFT_BUS_CONNECTOR.16
O_DB1: IC6.17 (B2), LEFT_BUS_CONNECTOR.14
O_DB2: IC6.16 (B3), LEFT_BUS_CONNECTOR.12
O_DB3: IC6.15 (B4), LEFT_BUS_CONNECTOR.10
O_DB4: IC6.14 (B5), LEFT_BUS_CONNECTOR.8
O_DB5: IC6.13 (B6), LEFT_BUS_CONNECTOR.6
O_DB6: IC6.12 (B7), LEFT_BUS_CONNECTOR.4
O_DB7: IC6.11 (B8), LEFT_BUS_CONNECTOR.2
SIG_1: IC4.4 (1Y), X5.1
SIG_2: IC4.7 (2Y), X5.2
SIG_3: IC4.9 (3Y), X5.3
SIG_4: IC4.12 (4Y), X5.4
SIG_5: IC5.4 (1Y), X5.5
SIG_6: IC5.7 (2Y), X5.6
SIG_7: IC5.9 (3Y), X5.7
SIG_8: IC5.12 (4Y), X5.8
VCC: C1.1, C2.1, C3.1, C4.1, C5.1, IC4.16 (VCC), IC5.16 (VCC), IC6.1 (DIR), IC6.20 (VCC), MEZZANINE.1, MEZZANINE.2, U$1.VCC, U$2.27 (!WE), U$2.28 (VCC), U$3.VCC, U$4.VCC, U$5.VCC, X11.1

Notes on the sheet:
Device IO
Signals Out
Right Hand Address Daisey Chain
Addr from Register
